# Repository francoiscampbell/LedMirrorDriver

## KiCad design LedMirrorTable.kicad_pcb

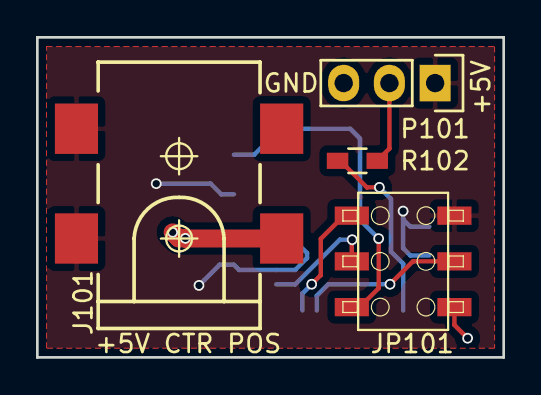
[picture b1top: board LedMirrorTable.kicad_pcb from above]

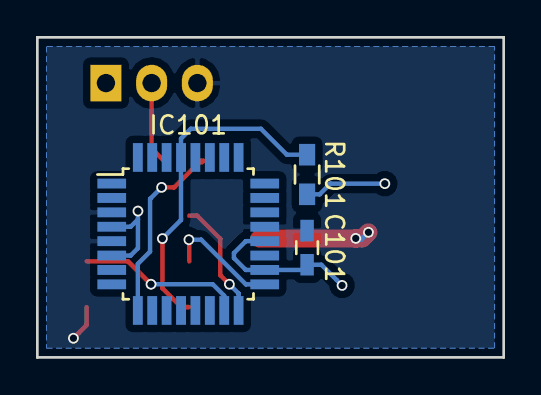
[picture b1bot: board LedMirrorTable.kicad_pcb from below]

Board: 2 copper layers, 25.9 x 17.8 mm, 7 parts (3 on the bottom side), 8 nets.

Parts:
C101: 100nF; C_0603_HandSoldering
IC101: ATMEGA328P-A; TQFP-32_7x7mm_Pitch0.8mm
J101: POWER_JACKSMD; SparkFun-Connectors-POWER_JACK_SMD
JP101: M03X2; SparkFun-Connectors-2X3_SMD
P101: CONN_01X03; Pin_Header_Straight_1x03
R101: 10k; R_0603_HandSoldering
R102: 470R; R_0603_HandSoldering

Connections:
+5V: C101.1, IC101.4, IC101.6, IC101.18, IC101.20, J101.VIN0, J101.VIN1, JP101.2, P101.1, R101.2
/D_OUT: IC101.9, R102.2
/D_STRIP: P101.2, R102.1
/PROG_MISO: IC101.16, JP101.1
/PROG_MOSI: IC101.15, JP101.4
/PROG_SCK: IC101.17, JP101.3
/RESET: IC101.29, JP101.5, R101.1
GND: C101.2, IC101.3, IC101.5, IC101.21, J101.GND, JP101.6, P101.3

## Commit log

2016-01-04 Kicad libraries initial commit
2016-01-04 Initial commit. Most parts laid out
2016-01-04 Added all components
2016-01-04 Added labels
2016-01-04 Removed unused libraries. Changed JST connector to 3-pin header
2016-01-04 Created PCB
2016-01-04 Fixed a few cosmetic errors
2016-01-04 Re-plotted gerbers
2016-01-04 Re-zipped new gerbers
